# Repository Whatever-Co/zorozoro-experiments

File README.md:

# ZOROZORO Experiments

This repository contains the experimental code for the ZOROZORO project, which controls 256 toio cubes simultaneously.

https://twitter.com/Saqoosha/status/1333233470143774720

## Architecture

| Module          | Role                                                                                              | Source code                                                                    |
| --------------- | ------------------------------------------------------------------------------------------------- | ------------------------------------------------------------------------------ |
| Cube Controller | Collects information from the Scanner and Bridge and sends out appropriate commands to each cube. | [`14-cubecontroller`](14-cubecontroller)                                       |
| Bridge          | Make a BLE connection with toio cubes and relay with Controller through TCP socket.               | [`13-unitycontroller2/PlatformIO/bridge/`](13-unitycontroller2/Arduino/bridge/)   |
| Scanner         | Detects a cube emitting an advertising signal and tells the contoller.                            | [`13-unitycontroller2/PlatformIO/scanner/`](13-unitycontroller2/Arduino/scanner/) |

## Hardware

- [Adafruit Feather nRF52840 Express](https://www.adafruit.com/product/4062)
- [Adafruit Ethernet FeatherWing](https://www.adafruit.com/product/3201)
- Ethernet Hub
- 5V/10A AC Adapter
- [Custom power distribution board](10-powerpcb/)

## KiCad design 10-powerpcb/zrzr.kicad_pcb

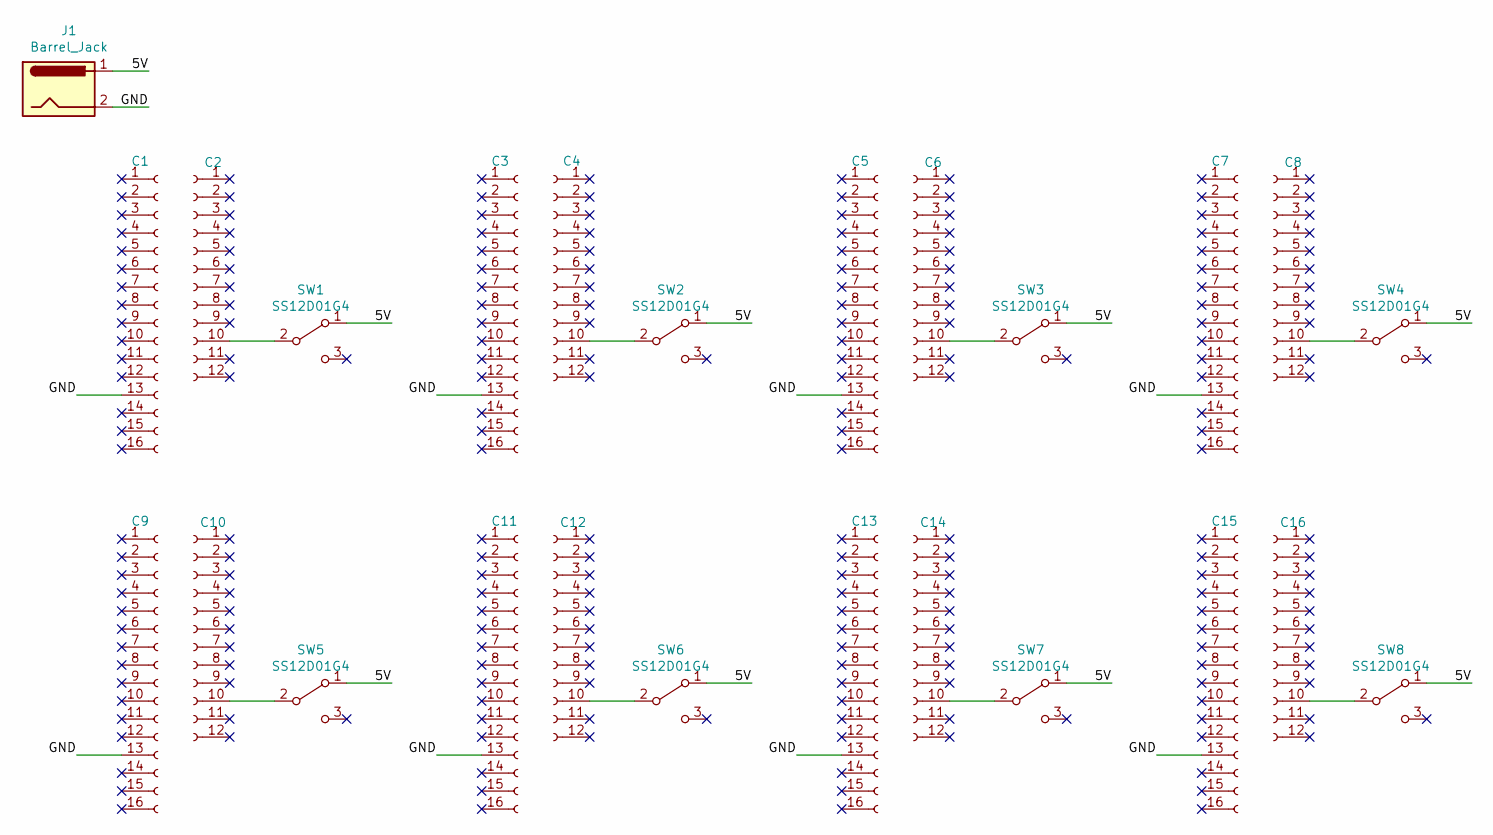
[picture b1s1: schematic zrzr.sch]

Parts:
C1, C3, C5, C7, C9, C11, C13, C15: Conn_01x16_Female; PinSocket_1x16_P2.54mm_Vertical
C2, C4, C6, C8, C10, C12, C14, C16: Conn_01x12_Female; PinSocket_1x12_P2.54mm_Vertical
J1: Barrel_Jack; BarrelJack_Horizontal
SW1, SW2, SW3, SW4, SW5, SW6, SW7, SW8: SS12D01G4; PinHeader_1x03_P2.54mm_Vertical

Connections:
/5V: J1.1, SW1.1 (A), SW2.1 (A), SW3.1 (A), SW4.1 (A), SW5.1 (A), SW6.1 (A), SW7.1 (A), SW8.1 (A)
/GND: C1.13, C3.13, C5.13, C7.13, C9.13, C11.13, C13.13, C15.13, J1.2
unnamed: C2.10, SW1.2 (B)
unnamed: C4.10, SW2.2 (B)
unnamed: C6.10, SW3.2 (B)
unnamed: C8.10, SW4.2 (B)
unnamed: C10.10, SW5.2 (B)
unnamed: C12.10, SW6.2 (B)
unnamed: C14.10, SW7.2 (B)
unnamed: C16.10, SW8.2 (B)

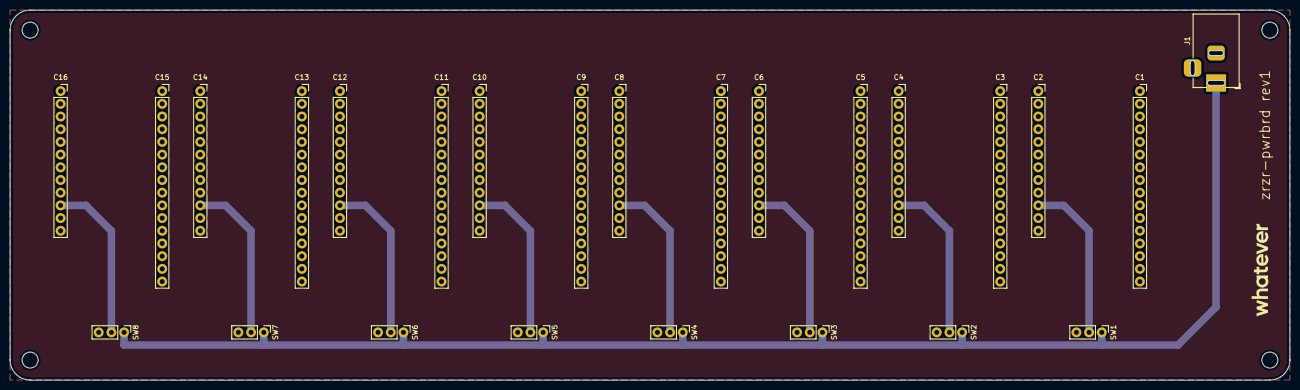
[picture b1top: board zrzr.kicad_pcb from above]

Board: 2 copper layers, 256.0 x 74.0 mm, 25 parts (0 on the bottom side), 10 nets.

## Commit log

2020-08-26 01-corebluetooth
2020-08-26 04-esp32
2020-08-26 05-adafruitnrf
2020-08-26 06-unitycontroller
2020-08-26 06: connected cube list
2020-08-26 06: disconnected
2020-08-26 06: split files, battery notification
2020-08-26 06: “controller”
2020-08-26 06: Client class
2020-08-26 06: scanner: reconnect if disconnected
2020-08-26 06: bridge: connect, disconnect message
2020-08-26 06: controller: connect cube
2020-08-26 06: refactor
2020-08-26 06: SetLamp
2020-08-27 06:wip
2020-08-27 07-mqtt
2020-08-27 06: Change protocol to mqtt
2020-08-27 06: Change lamp color according to the battery value
2020-08-28 06: Add UI
2020-08-28 06: Add ZLogger, ZString
2020-08-28 06: Replace logger to ZLogger
2020-08-28 06: scanner: publish while connected
2020-08-28 06: bridge: subscribe after init
2020-08-28 06: Add upload only task
2020-08-28 06: bridge: Send button event
2020-08-28 06: Cube manager
2020-08-28 08-adafruitmqtt
    Adafruit_MQTT_Library
2020-08-28 06: cleanup / refactor
2020-08-30 06: Change connection handling strategy
2020-08-30 06: Re-subscribe after reconnected
2020-08-30 06: Add internal mqtt server
2020-08-31 06: Sync position
2020-08-31 05: Send lamp command periodically
2020-08-31 06: Press button to rotate
2020-08-31 06: Control all cubes at once
2020-09-01 09-circuitpy
2020-09-01 05: Cube class
2020-09-01 05: All cubes are managed by static methods
2020-09-01 05: LampControl
2020-09-01 05: Upload task
2020-09-01 05: MotorControl
2020-09-01 05: Refactor
2020-09-02 05: Add more memory to SD
2020-09-02 05: Add SensorInfo
2020-09-02 05: IdInfo
2020-09-02 05: Grid
2020-09-08 06: nRF52 bridge
2020-09-08 06: Arduino: Refactor
2020-09-09 06: Handle newcube message on controller
2020-09-09 06: Replace with “arduino-mqtt”
    https://github.com/256dpi/arduino-mqtt
2020-09-09 06: Random rotate
2020-09-10 10-powerpcb
2020-09-14 11-simulator
2020-09-14 11: Optimize destination selection
2020-10-08 06: Scanner for nrf52
2020-10-08 06: Unity 2020.1.5f1
2020-10-14 06: Config
2020-10-14 06: Go around in circle
2020-10-15 06: Update ZString
2020-10-15 06: Add ImtStateMachine
2020-10-16 06: mqtt connection status led
2020-10-16 06: Remove state machine..
2020-10-16 06: Change neopixel with connected cube count
2020-10-20 06: Move directly by arrow keys
2020-10-21 06: scanner: add status led
2020-10-21 06: Send available slots count with /available message
2020-10-21 06: bridge: Periodically send availability
2020-10-27 06: Use custom tcp socket client to improve stability
2020-10-27 12-batterybenchmark
2020-10-28 13-unitycontroller2
2020-10-28 13: Multiple tcp clients
2020-10-28 13: Scanner implemented with raw tcp socket
2020-10-28 13: Replace scanner with raw tcp sorket version
2020-10-29 13: Accept multiple clients
2020-10-29 13: BridgeManager
2020-10-29 13: Close on app quit
2020-10-29 13: bridge: Handle connection failue
2020-10-30 13: bridge: Build “disconnected” topic without Arduino String
2020-10-30 13: Reset battery value on connected
2020-10-30 13: Cleanup
2020-10-30 13: bridge: tiny fix
2020-10-30 13: Use ZLogger
2020-11-02 13: connected dev sheet coords
2020-11-02 13: Constant speed
2020-11-02 13: bridge: Send “connected” message on reconnect
2020-11-02 13: Add hit test with another cubes
2020-11-05 13: Automatically start “go around” in it’s already in mode
2020-11-06 14-cubecontroller
    written in Rust
2020-11-06 13: Buld action buttons by script
2020-11-06 13: change port
2020-11-06 14: Parse some message types
2020-11-06 14: Add bridge mode
2020-11-06 14: Bidirectional inter-thread communication (WIP)
2020-11-07 14: Send message to bridges
2020-11-09 14: Parse other messages
2020-11-09 14: Send set lamp message
2020-11-09 14: CubeManager
2020-11-09 14: Add “iced” to build UIs
2020-11-09 14: Prevent repeating key events
2020-11-09 14: Run managers from inside App
2020-11-09 14: Split to bridge_manager.rs
2020-11-10 14: Connecting to cube manager (WIP)
2020-11-10 14: Replaced with crossbeam_channel
2020-11-10 14: SetLampAll is now working.
2020-11-10 14: Message param as ref
2020-11-10 14: Set battery status led
2020-11-11 14: Add channels to UI (not working…
2020-11-12 14: Remove iced...
2020-11-12 14: Add piston
2020-11-12 14: Draw cubes at current position
2020-11-12 14: Simplify option value check
2020-11-12 14: Press key to issue the command
2020-11-12 14: Add logging library
2020-11-12 14: Change color or press key
2020-11-13 14: Set random direction
2020-11-13 14: Add hit test
2020-11-13 14: Go around command (WIP)
2020-11-16 14: Move hit test into CubeManager
2020-11-16 14: Stop on hit something
2020-11-16 14: Handle data parsing error
2020-11-16 14: Add info text
2020-11-16 14: Move menu to bottom
2020-11-16 14: Add info log
2020-11-16 14: 1 key to set led color according to battery level
2020-11-16 14: Hide if cube position is missed
2020-11-16 14: Start go around if already started
2020-11-16 14: Mat coord
2020-11-17 Fix window resize bug
    https://github.com/PistonDevelopers/graphics/issues/1129#issuecomment-666368010
2020-11-17 14: Draw connecting status
2020-11-17 13: Send available slots even if it’s zero
2020-11-17 14: Change status opacity according to the time from receiving last message
2020-11-18 14: Message parse error handling
2020-11-18 14: Faster fade-out
2020-11-18 14: Process all messages in received buffer
2020-11-18 14: Increase receive buffer size
2020-11-19 13: Add blink task to check the alive status
2020-11-19 13: Check actual topic length to detect corrupted or not
2020-11-19 13: Send mac address
2020-11-19 14: Assign ID according to its mac address
2020-11-19 14: Disable hit test when it’s not in “Go Around” mode
    Hit tist run up to 100fps
2020-11-19 14: Use IP address instead of MAC
2020-11-19 13: Same code as bridge
2020-11-19 13: Remove MAC address
2020-11-20 13: Sensor config
2020-11-20 14: Largest mat coord
2021-11-25 Add README.md
2021-11-25 Add LICENSE
